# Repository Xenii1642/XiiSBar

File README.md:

<picture> <source media="(prefers-color-scheme: dark)" srcset="images/XiiSBar_logo.png">  </picture> 

The XiiSBar is a small portable Sensor Bar. It is useful to fully use the WiiMote on your portable Wii. 

Its small form factor means that you can put it under a Xii-Boy Pocket stand !

Check this Bitbuilt Thread for further informations: [XiiSBar's Bitbuilt Thread](https://bitbuilt.net/forums/index.php?threads/the-xiisbar.6623/)

## PCB
First, you'll need to order the XiiSBar PCB through [JLCPCB](https://jlcpcb.com/), [PCBWay](https://www.pcbway.com/), [Next PCB](https://www.nextpcb.com/) or  the manufacturer you prefer. 
I personally order mine through [JLCPCB](https://jlcpcb.com/) because it's the cheapest. 

Generally, PCBWay offers a better PCB quality. However, the XiiSBar PCB is very simple, and doesn't require the best quality.
#
Once you've chosen you're manufacturer, upload the [XiiSBar PCB Geber file](https://github.com/Xenii1642/XiiSBar/tree/main/PCB%20Files/Gerber). 

Let the settings by default. Only change the color if you want. Once your order is done, you'll have to order the components for the PCB.

All the components are listed in the [BOM file](https://github.com/Xenii1642/XiiSBar/blob/main/BOM.pdf). I personally ordered them through [Digikey](https://www.digikey.com/en/products).
#
Once you have the PCB and the components, you'll have to assemble it. Each component on the [BOM file](https://github.com/Xenii1642/XiiSBar/blob/main/BOM.pdf) correspond to each label on the PCB.
I used a solder iron set to 360℃ (680℉) with Lead-Free solder. Once the assembly is done, your PCB should look like this:

## Assembly

This is all the parts you need to build a XiiSBar. 
All the STLs for the 3D printed parts are in the STL folder 😉

#
First, put the switch slider in the switch hole of the case. Then, rotate the board in place.

⚠ This last part could be a bit tricky considering the small tolerances ⚠

After that, you'll need to screew the board in place. Use the M1.7x4 ones.

Place this piece as shown below and then fold it. Do the same thing for the other black piece.

⚠ If you deceided to solder the optional LED2, you have to use the "Right + LED" piece instead. ⚠

Now, take this piece and place it like this. You should be able to close the case.

Take two M1.7x6 screws and screw the case.

Finally, take the battery cover and the clip. Put both parts together.⚠ You might need some super glue ⚠

Finally, put the battery cover on the case and close it ! That's it !

If you have any question during the assembly, about the files or other, don't hesistate to ask me 👍

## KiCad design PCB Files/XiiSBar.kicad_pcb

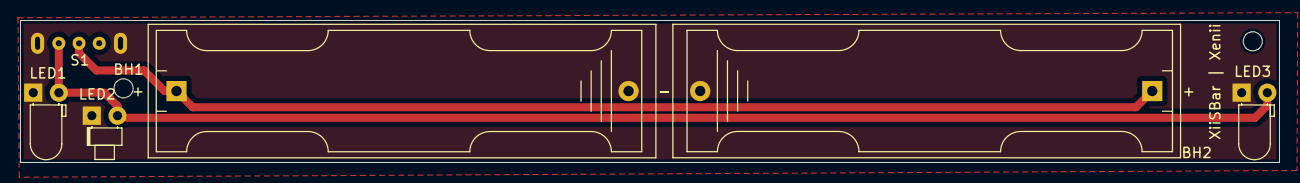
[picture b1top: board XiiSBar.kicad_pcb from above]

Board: 2 copper layers, 124.5 x 14.0 mm, 6 parts (0 on the bottom side), 3 nets.

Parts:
BT1, BT2: Battery_Cell; BatteryHolder_Keystone_2466_1xAAA
D1, D2: LED; LED_D3.0mm_Horizontal_O1.27mm_Z10.0mm
D3: LED; LED_D1.8mm_W1.8mm_H2.4mm_Horizontal_O1.27mm_Z1.6mm
U1: SLW-864587-2A-RA-N-D

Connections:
GND: BT1.2 (-), BT2.2 (-), D1.1 (K), D2.1 (K), D3.1 (K), U1.4, U1.5
unnamed: BT1.1 (+), BT2.1 (+), U1.2
unnamed: D1.2 (A), D2.2 (A), D3.2 (A), U1.3

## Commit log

2024-10-18 README.md
2024-10-24 Rename Trap.stl to Battery Cover.stl
